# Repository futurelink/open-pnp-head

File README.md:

Versatile 4-nozzle PNP head controller
---

This controller was designed to be built into most of DIY pick-n-place machine heads.

### Features:
 - STM32F103C8T6 cheap MCU running on 72MHz
 - RS-485 control port
 - 4 rotary steppers running low-power STSPIN220 drivers
 - 2 up-down steppers running Pololu modules on your taste
 - 4 vacuum sensors to control part presence and place success
 - 4 isolated end-stop ports for home position identification
 - 4 isolated AO3400 MOSFET-driven ports to connect valves, solenoids etc.
 - head top light either WS2812 or LED-strip (5 or 12v)
 - Small size 80x65mm
 - No parts smaller than 0603 so can be hand-built.

### Board render:

### Disclaimer

This project is still in development, and it's not production ready.

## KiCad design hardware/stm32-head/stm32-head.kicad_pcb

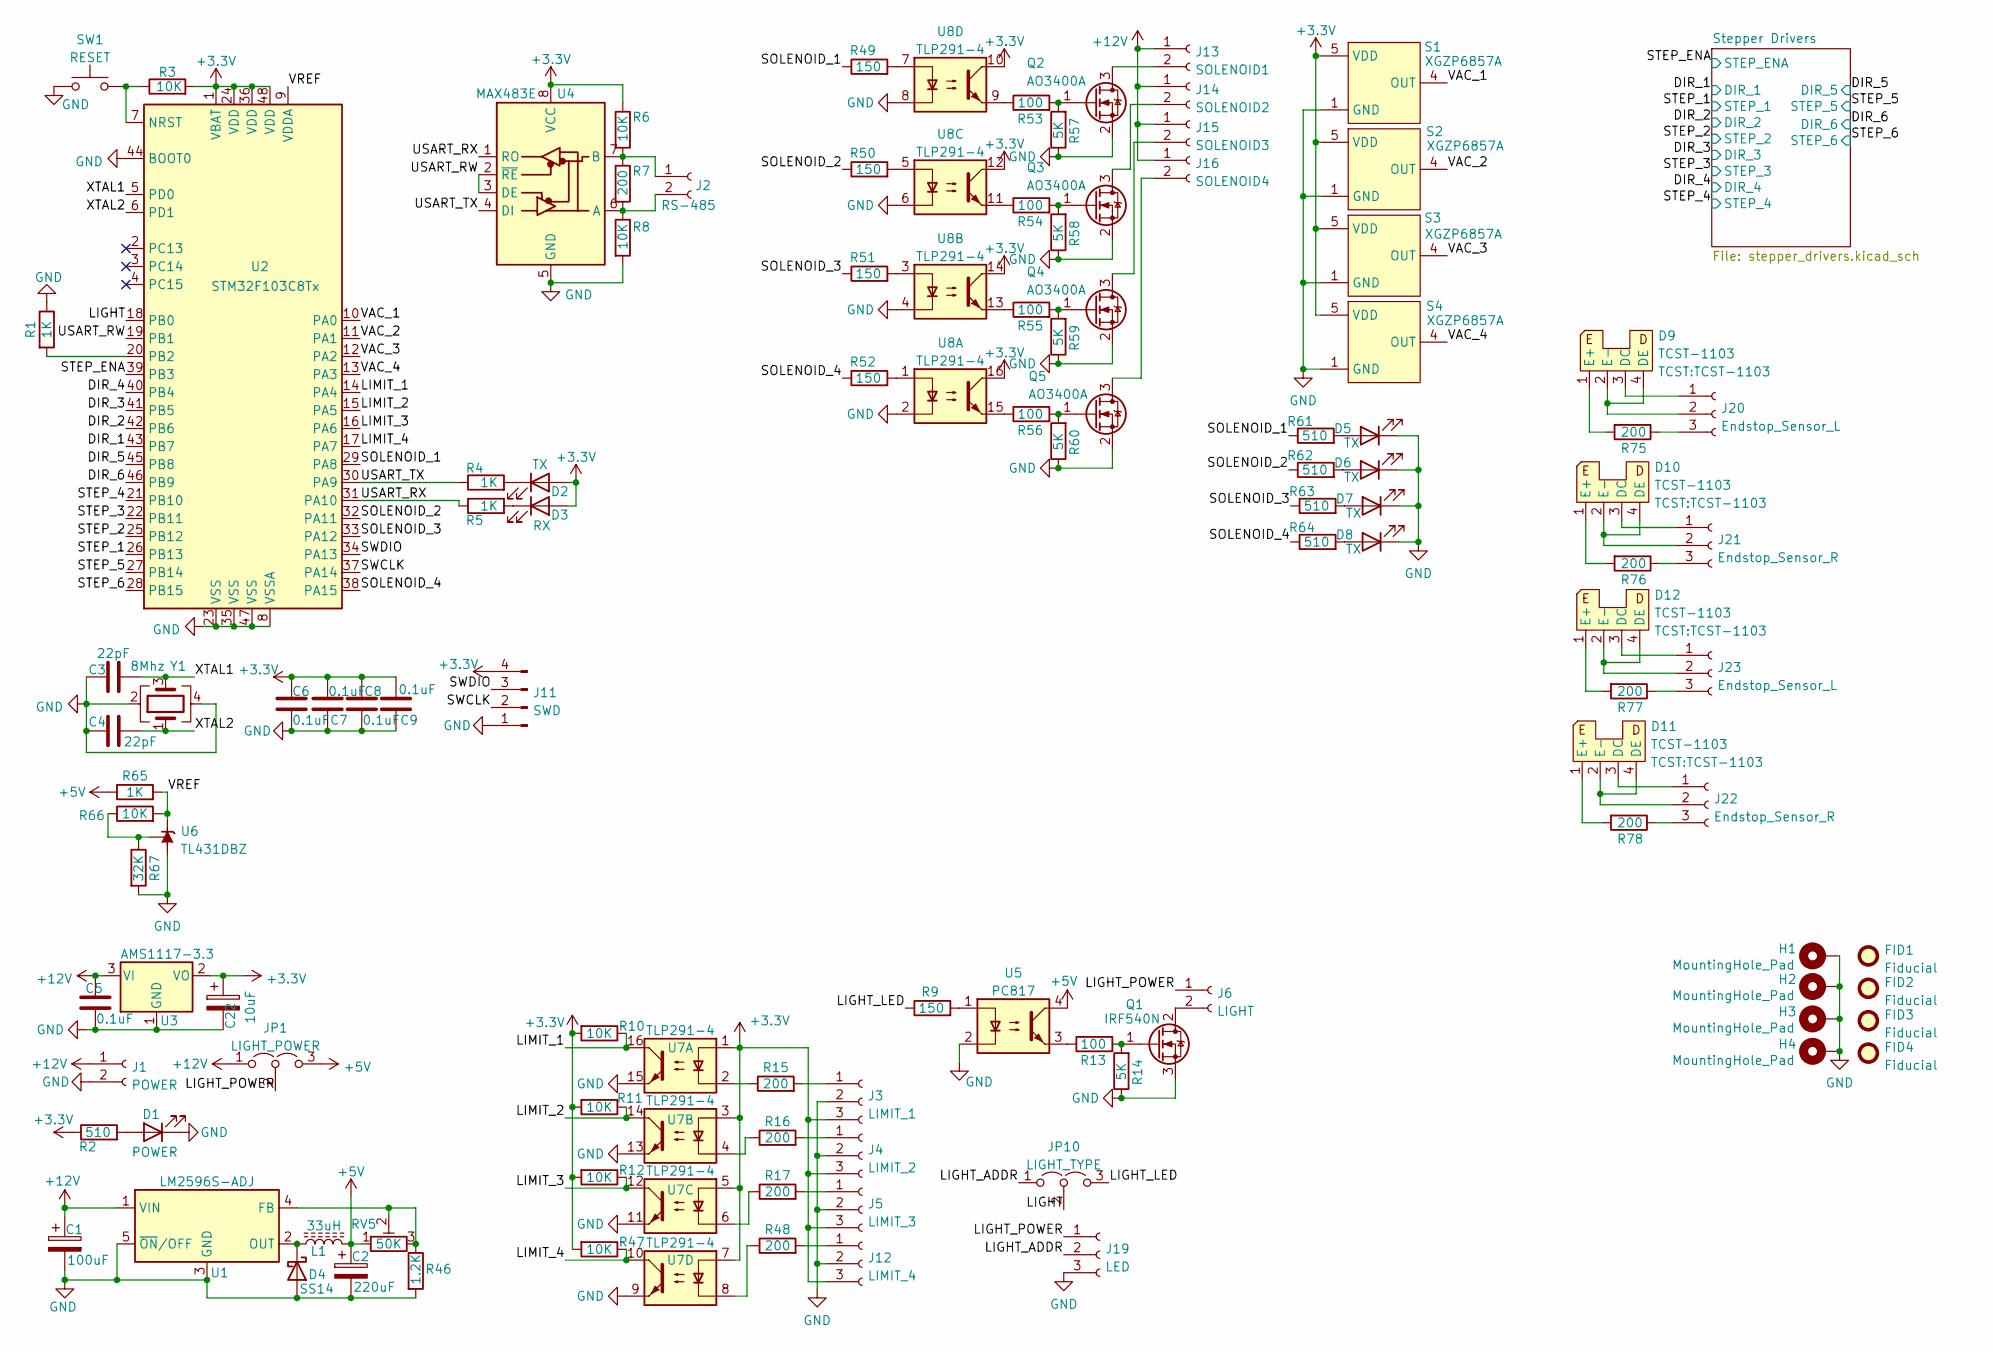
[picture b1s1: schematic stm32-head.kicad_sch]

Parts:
C1: 100uF; CP_Elec_6.3x5.9
C2: 220uF; CP_EIA-7343-31_Kemet-D
C3, C4: 22pF; C_0603_1608Metric
C5, C6, C7, C8, C9: 0.1uF; C_0603_1608Metric
C22: 10uF; CP_EIA-3216-12_Kemet-S
D1: POWER; LED_0603_1608Metric
D2, D5, D6, D7, D8: TX; LED_0603_1608Metric
D3: RX; LED_0603_1608Metric
D4: SS14; D_SMB
D9, D10, D11, D12: TCST-1103
FID1, FID2, FID3, FID4: Fiducial; Fiducial_0.5mm_Mask1mm
H1, H2, H3, H4: MountingHole_Pad; MountingHole_2.5mm_Pad_Via
J1: POWER; JST_XH_B2B-XH-A_1x02_P2.50mm_Vertical
J2: RS-485; JST_EH_B2B-EH-A_1x02_P2.50mm_Vertical
J3: LIMIT_1; JST_GH_BM03B-GHS-TBT_1x03-1MP_P1.25mm_Vertical
J4: LIMIT_2; JST_GH_BM03B-GHS-TBT_1x03-1MP_P1.25mm_Vertical
J5: LIMIT_3; JST_GH_BM03B-GHS-TBT_1x03-1MP_P1.25mm_Vertical
J6: LIGHT; JST_GH_BM02B-GHS-TBT_1x02-1MP_P1.25mm_Vertical
J11: SWD; JST_EH_B4B-EH-A_1x04_P2.50mm_Vertical
J12: LIMIT_4; JST_GH_BM03B-GHS-TBT_1x03-1MP_P1.25mm_Vertical
J13: SOLENOID1; JST_EH_B2B-EH-A_1x02_P2.50mm_Vertical
J14: SOLENOID2; JST_EH_B2B-EH-A_1x02_P2.50mm_Vertical
J15: SOLENOID3; JST_EH_B2B-EH-A_1x02_P2.50mm_Vertical
J16: SOLENOID4; JST_EH_B2B-EH-A_1x02_P2.50mm_Vertical
J19: LED; JST_EH_B3B-EH-A_1x03_P2.50mm_Vertical
J20, J23: Endstop_Sensor_L; JST_GH_SM03B-GHS-TB_1x03-1MP_P1.25mm_Horizontal
J21, J22: Endstop_Sensor_R; JST_GH_SM03B-GHS-TB_1x03-1MP_P1.25mm_Horizontal
JP1: LIGHT_POWER; PinHeader_1x03_P2.54mm_Vertical
JP10: LIGHT_TYPE; PinHeader_1x03_P2.54mm_Vertical
L1: 33uH; L_6.3x6.3_H3
Q1: IRF540N; TO-252-3_TabPin2
Q2, Q3, Q4, Q5: AO3400A; SOT-23
R1, R4, R5, R65: 1K; R_0603_1608Metric
R2, R61, R62, R63, R64: 510; R_0603_1608Metric
R3, R6, R8, R10, R11, R12, R47, R66: 10K; R_0603_1608Metric
R7, R15, R16, R17, R48, R75, R76, R77, R78: 200; R_0603_1608Metric
R9, R49, R50, R51, R52: 150; R_0603_1608Metric
R13, R53, R54, R55, R56: 100; R_0603_1608Metric
R14, R57, R58, R59, R60: 5K; R_0603_1608Metric
R46: 1.2K; R_0603_1608Metric
R67: 32K; R_0603_1608Metric
RV5: 50K; Potentiometer_Bourns_TC33X_Vertical
S1, S2, S3, S4: XGZP6857A; XGZP_Sensor_THT
SW1: RESET; SW_SPST_FSMSM
U1: LM2596S-ADJ; TO-263-5_TabPin3
U2: STM32F103C8Tx; LQFP-48_7x7mm_P0.5mm
U3: AMS1117-3.3; SOT-223-3_TabPin2
U4: MAX483E; SO-8_3.9x4.9mm_P1.27mm
U5: PC817; DIP-4_W7.62mm
U6: TL431DBZ; SOT-23
U7, U8: TLP291-4; SOIC-16_4.55x10.3mm_P1.27mm
Y1: 8Mhz; Crystal_SMD_3225-4Pin_3.2x2.5mm

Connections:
+3.3V: C6.2, C7.2, C8.2, C9.2, C22.1, D2.2 (A), D3.2 (A), J3.3, J4.3, J5.3, J11.4, J12.3, R2.1, R3.2, R6.1, R10.2, R11.2, R12.2, R47.2, S1.5 (VDD), S2.5 (VDD), S3.5 (VDD), S4.5 (VDD), U2.1 (VBAT), U2.24 (VDD), U2.36 (VDD), U2.48 (VDD), U3.2 (VO), U4.8 (VCC), U7.1, U7.3, U7.5, U7.7, U8.10, U8.12, U8.14, U8.16; also elsewhere on the board
+5V: C2.1, JP1.3 (B), L1.2, R65.1, RV5.1, U5.4; also elsewhere on the board
+12V: C1.1, C5.2, J1.1, J13.1, J14.1, J15.1, J16.1, JP1.1 (A), U1.1 (VIN), U3.3 (VI); also elsewhere on the board
/DIR_1: U2.43 (PB7); also elsewhere on the board
/DIR_2: U2.42 (PB6); also elsewhere on the board
/DIR_3: U2.41 (PB5); also elsewhere on the board
/DIR_4: U2.40 (PB4); also elsewhere on the board
/DIR_5: U2.45 (PB8); also elsewhere on the board
/DIR_6: U2.46 (PB9); also elsewhere on the board
/LIGHT: JP10.2 (C), U2.18 (PB0)
/LIGHT_ADDR: J19.2, JP10.1 (A)
/LIGHT_LED: JP10.3 (B), R9.1
/LIGHT_POWER: J6.1, J19.1, JP1.2 (C)
/LIMIT_1: R10.1, U2.14 (PA4), U7.16
/LIMIT_2: R11.1, U2.15 (PA5), U7.14
/LIMIT_3: R12.1, U2.16 (PA6), U7.12
/LIMIT_4: R47.1, U2.17 (PA7), U7.10
/SOLENOID_1: R49.1, R61.1, U2.29 (PA8)
/SOLENOID_2: R50.1, R62.1, U2.32 (PA11)
/SOLENOID_3: R51.1, R63.1, U2.33 (PA12)
/SOLENOID_4: R52.1, R64.1, U2.38 (PA15)
/STEP_1: U2.26 (PB13); also elsewhere on the board
/STEP_2: U2.25 (PB12); also elsewhere on the board
/STEP_3: U2.22 (PB11); also elsewhere on the board
/STEP_4: U2.21 (PB10); also elsewhere on the board
/STEP_5: U2.27 (PB14); also elsewhere on the board
/STEP_6: U2.28 (PB15); also elsewhere on the board
/STEP_ENA: U2.39 (PB3); also elsewhere on the board
/SWCLK: J11.2, U2.37 (PA14)
/SWDIO: J11.3, U2.34 (PA13)
/USART_RW: U2.19 (PB1), U4.2 (~RE), U4.3 (DE)
/USART_RX: R5.1, U2.31 (PA10), U4.1 (RO)
/USART_TX: R4.1, U2.30 (PA9), U4.4 (DI)
/VAC_1: S1.4 (OUT), U2.10 (PA0)
/VAC_2: S2.4 (OUT), U2.11 (PA1)
/VAC_3: S3.4 (OUT), U2.12 (PA2)
/VAC_4: S4.4 (OUT), U2.13 (PA3)
/VREF: R65.2, R66.2, U2.9 (VDDA), U6.1 (K)
/XTAL1: C3.2, U2.5 (PD0), Y1.3
/XTAL2: C4.2, U2.6 (PD1), Y1.1
GND: C1.2, C2.2, C3.1, C4.1, C5.1, C6.1, C7.1, C8.1, C9.1, C22.2, D1.1 (K), D4.2 (A), D5.1 (K), D6.1 (K), D7.1 (K), D8.1 (K), H1.1, H2.1, H3.1, H4.1, J1.2, J3.2, J4.2, J5.2, J11.1, J12.2, J19.3, Q1.3 (S), Q2.2 (S), Q3.2 (S), Q4.2 (S), Q5.2 (S), R1.1, R8.2, R14.1, R46.2, R57.1, R58.1, R59.1, R60.1, R67.2, S1.1 (GND), S2.1 (GND), S3.1 (GND), S4.1 (GND), SW1.1, U1.3 (GND), U1.5 (~ON/OFF), U2.8 (VSSA), U2.23 (VSS), U2.35 (VSS), U2.44 (BOOT0), U2.47 (VSS), U3.1 (GND), U4.5 (GND), U5.2, U6.3 (A), U7.9, U7.11, U7.13, U7.15, U8.2, U8.4, U8.6, U8.8, Y1.2, Y1.4; also elsewhere on the board
unnamed: D1.2 (A), R2.2
unnamed: D2.1 (K), R4.2
unnamed: D3.1 (K), R5.2
unnamed: D4.1 (K), L1.1, U1.2 (OUT)
unnamed: D5.2 (A), R61.2
unnamed: D6.2 (A), R62.2
unnamed: D7.2 (A), R63.2
unnamed: D8.2 (A), R64.2
unnamed: D9.1 (E+), R75.2
unnamed: D9.2 (E-), D9.4 (DE), J20.2
unnamed: D9.3 (DC), J20.1
unnamed: D10.1 (E+), R76.2
unnamed: D10.2 (E-), D10.4 (DE), J21.2
unnamed: D10.3 (DC), J21.1
unnamed: D11.1 (E+), R78.2
unnamed: D11.2 (E-), D11.4 (DE), J22.2
unnamed: D11.3 (DC), J22.1
unnamed: D12.1 (E+), R77.2
unnamed: D12.2 (E-), D12.4 (DE), J23.2
unnamed: D12.3 (DC), J23.1
unnamed: J2.1, R6.2, R7.1, U4.7 (B)
unnamed: J2.2, R7.2, R8.1, U4.6 (A)
unnamed: J3.1, R15.2
unnamed: J4.1, R16.2
unnamed: J5.1, R17.2
unnamed: J6.2, Q1.2 (D)
unnamed: J12.1, R48.2
unnamed: J13.2, Q2.3 (D)
unnamed: J14.2, Q3.3 (D)
unnamed: J15.2, Q4.3 (D)
unnamed: J16.2, Q5.3 (D)
unnamed: J20.3, R75.1
unnamed: J21.3, R76.1
unnamed: J22.3, R78.1
unnamed: J23.3, R77.1
unnamed: Q1.1 (G), R13.2, R14.2
unnamed: Q2.1 (G), R53.2, R57.2
unnamed: Q3.1 (G), R54.2, R58.2
unnamed: Q4.1 (G), R55.2, R59.2
unnamed: Q5.1 (G), R56.2, R60.2
unnamed: R1.2, U2.20 (PB2)
unnamed: R3.1, SW1.2, U2.7 (NRST)
unnamed: R9.2, U5.1
unnamed: R13.1, U5.3
unnamed: R15.1, U7.2
unnamed: R16.1, U7.4
unnamed: R17.1, U7.6
unnamed: R46.1, RV5.2, RV5.3, U1.4 (FB)
unnamed: R48.1, U7.8
unnamed: R49.2, U8.7
unnamed: R50.2, U8.5
unnamed: R51.2, U8.3
unnamed: R52.2, U8.1
unnamed: R53.1, U8.9
unnamed: R54.1, U8.11
unnamed: R55.1, U8.13
unnamed: R56.1, U8.15
unnamed: R66.1, R67.1, U6.2 (REF)

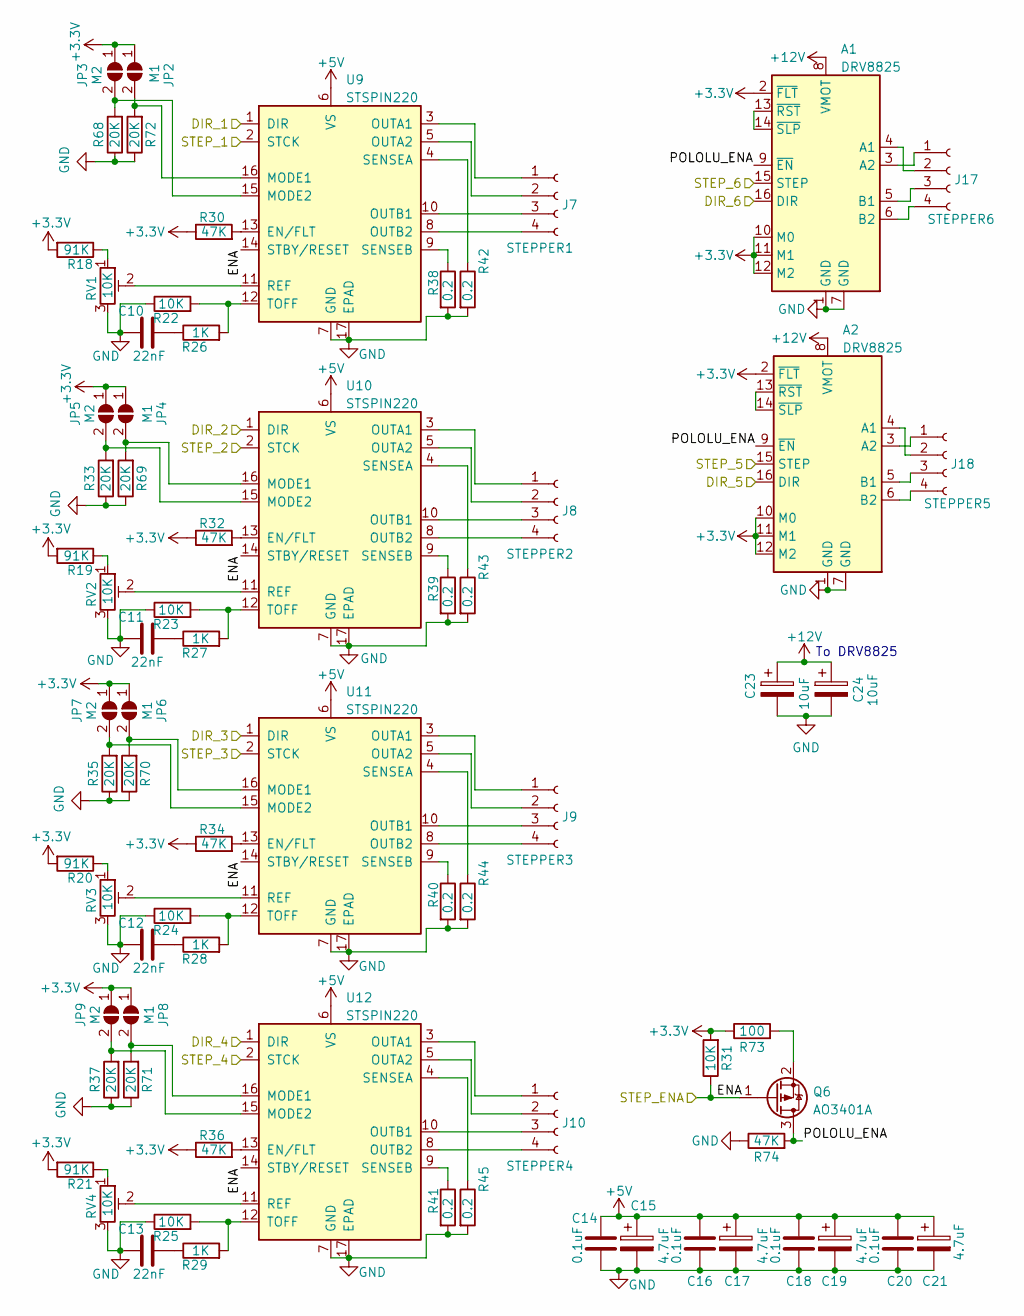
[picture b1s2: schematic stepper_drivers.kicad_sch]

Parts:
A1, A2: DRV8825; Pololu_Breakout-16_15.2x20.3mm
C10, C11, C12, C13: 22nF; C_0603_1608Metric
C14, C16, C18, C20: 0.1uF; C_0603_1608Metric
C15, C17, C19, C21: 4.7uF; CP_EIA-3216-10_Kemet-I
C23, C24: 10uF; CP_Elec_6.3x5.9
J7: STEPPER1; JST_GH_SM04B-GHS-TB_1x04-1MP_P1.25mm_Horizontal
J8: STEPPER2; JST_GH_SM04B-GHS-TB_1x04-1MP_P1.25mm_Horizontal
J9: STEPPER3; JST_GH_SM04B-GHS-TB_1x04-1MP_P1.25mm_Horizontal
J10: STEPPER4; JST_GH_SM04B-GHS-TB_1x04-1MP_P1.25mm_Horizontal
J17: STEPPER6; JST_GH_SM04B-GHS-TB_1x04-1MP_P1.25mm_Horizontal
J18: STEPPER5; JST_GH_SM04B-GHS-TB_1x04-1MP_P1.25mm_Horizontal
JP2, JP4, JP6, JP8: M1; SolderJumper-2_P1.3mm_Open_RoundedPad1.0x1.5mm
JP3, JP5, JP7, JP9: M2; SolderJumper-2_P1.3mm_Open_RoundedPad1.0x1.5mm
Q6: AO3401A; SOT-23
R18, R19, R20, R21: 91K; R_0603_1608Metric
R22, R23, R24, R25, R31: 10K; R_0603_1608Metric
R26, R27, R28, R29: 1K; R_0603_1608Metric
R30, R32, R34, R36, R74: 47K; R_0603_1608Metric
R33, R35, R37, R68, R69, R70, R71, R72: 20K; R_0603_1608Metric
R38, R39, R40, R41, R42, R43, R44, R45: 0.2; R_1206_3216Metric
R73: 100; R_0603_1608Metric
RV1, RV2, RV3, RV4: 10K; Potentiometer_Bourns_TC33X_Vertical
U9, U10, U11, U12: STSPIN220; VQFN-16-1EP_3x3mm_P0.5mm_EP1.8x1.8mm

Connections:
+3.3V: A1.2 (~FLT), A1.10 (M0), A1.11 (M1), A1.12 (M2), A2.2 (~FLT), A2.10 (M0), A2.11 (M1), A2.12 (M2), JP2.1 (A), JP3.1 (A), JP4.1 (A), JP5.1 (A), JP6.1 (A), JP7.1 (A), JP8.1 (A), JP9.1 (A), R18.2, R19.2, R20.2, R21.2, R30.1, R31.2, R32.1, R34.1, R36.1, R73.1; also elsewhere on the board
+5V: C14.1, C15.1, C16.1, C17.1, C18.1, C19.1, C20.1, C21.1, U9.6 (VS), U10.6 (VS), U11.6 (VS), U12.6 (VS); also elsewhere on the board
+12V: A1.8 (VMOT), A2.8 (VMOT), C23.1, C24.1; also elsewhere on the board
/DIR_1: U9.1 (DIR); also elsewhere on the board
/DIR_2: U10.1 (DIR); also elsewhere on the board
/DIR_3: U11.1 (DIR); also elsewhere on the board
/DIR_4: U12.1 (DIR); also elsewhere on the board
/DIR_5: A2.16 (DIR); also elsewhere on the board
/DIR_6: A1.16 (DIR); also elsewhere on the board
/STEP_1: U9.2 (STCK); also elsewhere on the board
/STEP_2: U10.2 (STCK); also elsewhere on the board
/STEP_3: U11.2 (STCK); also elsewhere on the board
/STEP_4: U12.2 (STCK); also elsewhere on the board
/STEP_5: A2.15 (STEP); also elsewhere on the board
/STEP_6: A1.15 (STEP); also elsewhere on the board
/STEP_ENA: Q6.1 (G), R31.1, U9.14 (STBY/RESET), U10.14 (STBY/RESET), U11.14 (STBY/RESET), U12.14 (STBY/RESET); also elsewhere on the board
/Stepper Drivers/POLOLU_ENA: A1.9 (~EN), A2.9 (~EN), Q6.3 (D), R74.2
GND: A1.1 (GND), A1.7 (GND), A2.1 (GND), A2.7 (GND), C10.1, C11.1, C12.1, C13.1, C14.2, C15.2, C16.2, C17.2, C18.2, C19.2, C20.2, C21.2, C23.2, C24.2, R22.1, R23.1, R24.1, R25.1, R33.1, R35.1, R37.1, R38.2, R39.2, R40.2, R41.2, R42.2, R43.2, R44.2, R45.2, R68.1, R69.1, R70.1, R71.1, R72.1, R74.1, RV1.3, RV2.3, RV3.3, RV4.3, U9.7 (GND), U9.17 (EPAD), U10.7 (GND), U10.17 (EPAD), U11.7 (GND), U11.17 (EPAD), U12.7 (GND), U12.17 (EPAD); also elsewhere on the board
unnamed: A1.3 (A2), J17.1
unnamed: A1.4 (A1), J17.2
unnamed: A1.5 (B1), J17.3
unnamed: A1.6 (B2), J17.4
unnamed: A1.13 (~RST), A1.14 (~SLP)
unnamed: A2.3 (A2), J18.1
unnamed: A2.4 (A1), J18.2
unnamed: A2.5 (B1), J18.3
unnamed: A2.6 (B2), J18.4
unnamed: A2.13 (~RST), A2.14 (~SLP)
unnamed: C10.2, R26.1
unnamed: C11.2, R27.1
unnamed: C12.2, R28.1
unnamed: C13.2, R29.1
unnamed: J7.1, U9.3 (OUTA1)
unnamed: J7.2, U9.5 (OUTA2)
unnamed: J7.3, U9.10 (OUTB1)
unnamed: J7.4, U9.8 (OUTB2)
unnamed: J8.1, U10.3 (OUTA1)
unnamed: J8.2, U10.5 (OUTA2)
unnamed: J8.3, U10.10 (OUTB1)
unnamed: J8.4, U10.8 (OUTB2)
unnamed: J9.1, U11.3 (OUTA1)
unnamed: J9.2, U11.5 (OUTA2)
unnamed: J9.3, U11.10 (OUTB1)
unnamed: J9.4, U11.8 (OUTB2)
unnamed: J10.1, U12.3 (OUTA1)
unnamed: J10.2, U12.5 (OUTA2)
unnamed: J10.3, U12.10 (OUTB1)
unnamed: J10.4, U12.8 (OUTB2)
unnamed: JP2.2 (B), R72.2, U9.16 (MODE1)
unnamed: JP3.2 (B), R68.2, U9.15 (MODE2)
unnamed: JP4.2 (B), R69.2, U10.16 (MODE1)
unnamed: JP5.2 (B), R33.2, U10.15 (MODE2)
unnamed: JP6.2 (B), R70.2, U11.16 (MODE1)
unnamed: JP7.2 (B), R35.2, U11.15 (MODE2)
unnamed: JP8.2 (B), R71.2, U12.16 (MODE1)
unnamed: JP9.2 (B), R37.2, U12.15 (MODE2)
unnamed: Q6.2 (S), R73.2
unnamed: R18.1, RV1.1
unnamed: R19.1, RV2.1
unnamed: R20.1, RV3.1
unnamed: R21.1, RV4.1
unnamed: R22.2, R26.2, U9.12 (TOFF)
unnamed: R23.2, R27.2, U10.12 (TOFF)
unnamed: R24.2, R28.2, U11.12 (TOFF)
unnamed: R25.2, R29.2, U12.12 (TOFF)
unnamed: R30.2, U9.13 (EN/FLT)
unnamed: R32.2, U10.13 (EN/FLT)
unnamed: R34.2, U11.13 (EN/FLT)
unnamed: R36.2, U12.13 (EN/FLT)
unnamed: R38.1, U9.9 (SENSEB)
unnamed: R39.1, U10.9 (SENSEB)
unnamed: R40.1, U11.9 (SENSEB)
unnamed: R41.1, U12.9 (SENSEB)
unnamed: R42.1, U9.4 (SENSEA)
unnamed: R43.1, U10.4 (SENSEA)
unnamed: R44.1, U11.4 (SENSEA)
unnamed: R45.1, U12.4 (SENSEA)
unnamed: RV1.2, U9.11 (REF)
unnamed: RV2.2, U10.11 (REF)
unnamed: RV3.2, U11.11 (REF)
unnamed: RV4.2, U12.11 (REF)

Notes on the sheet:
To DRV8825

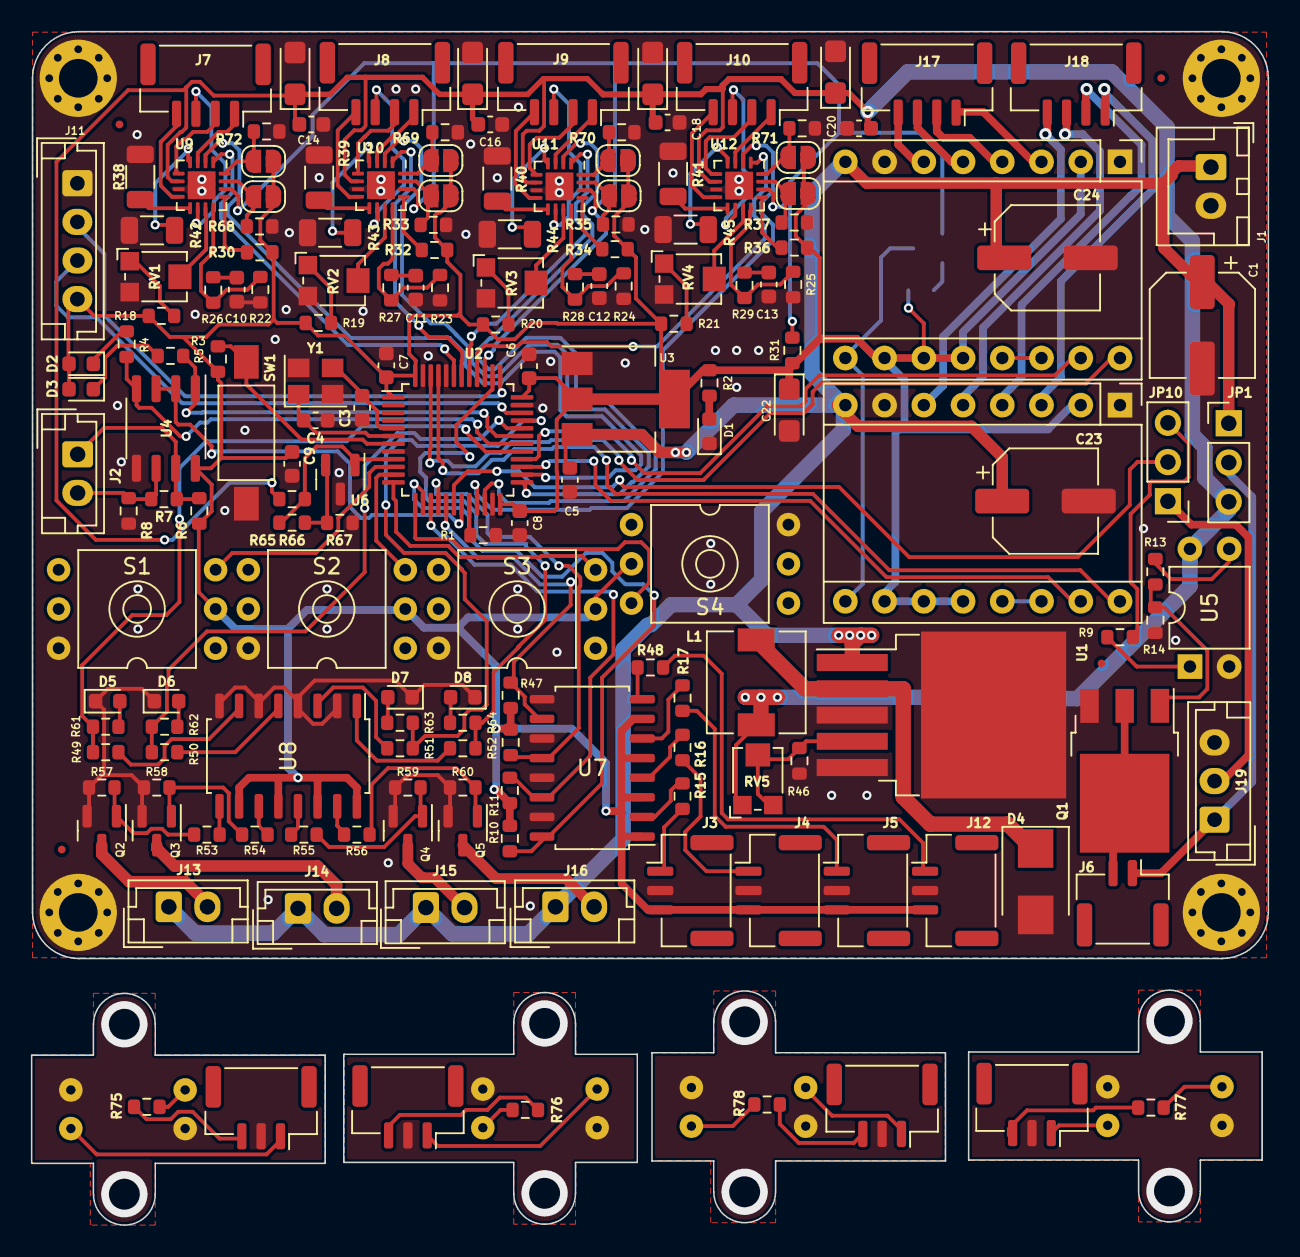
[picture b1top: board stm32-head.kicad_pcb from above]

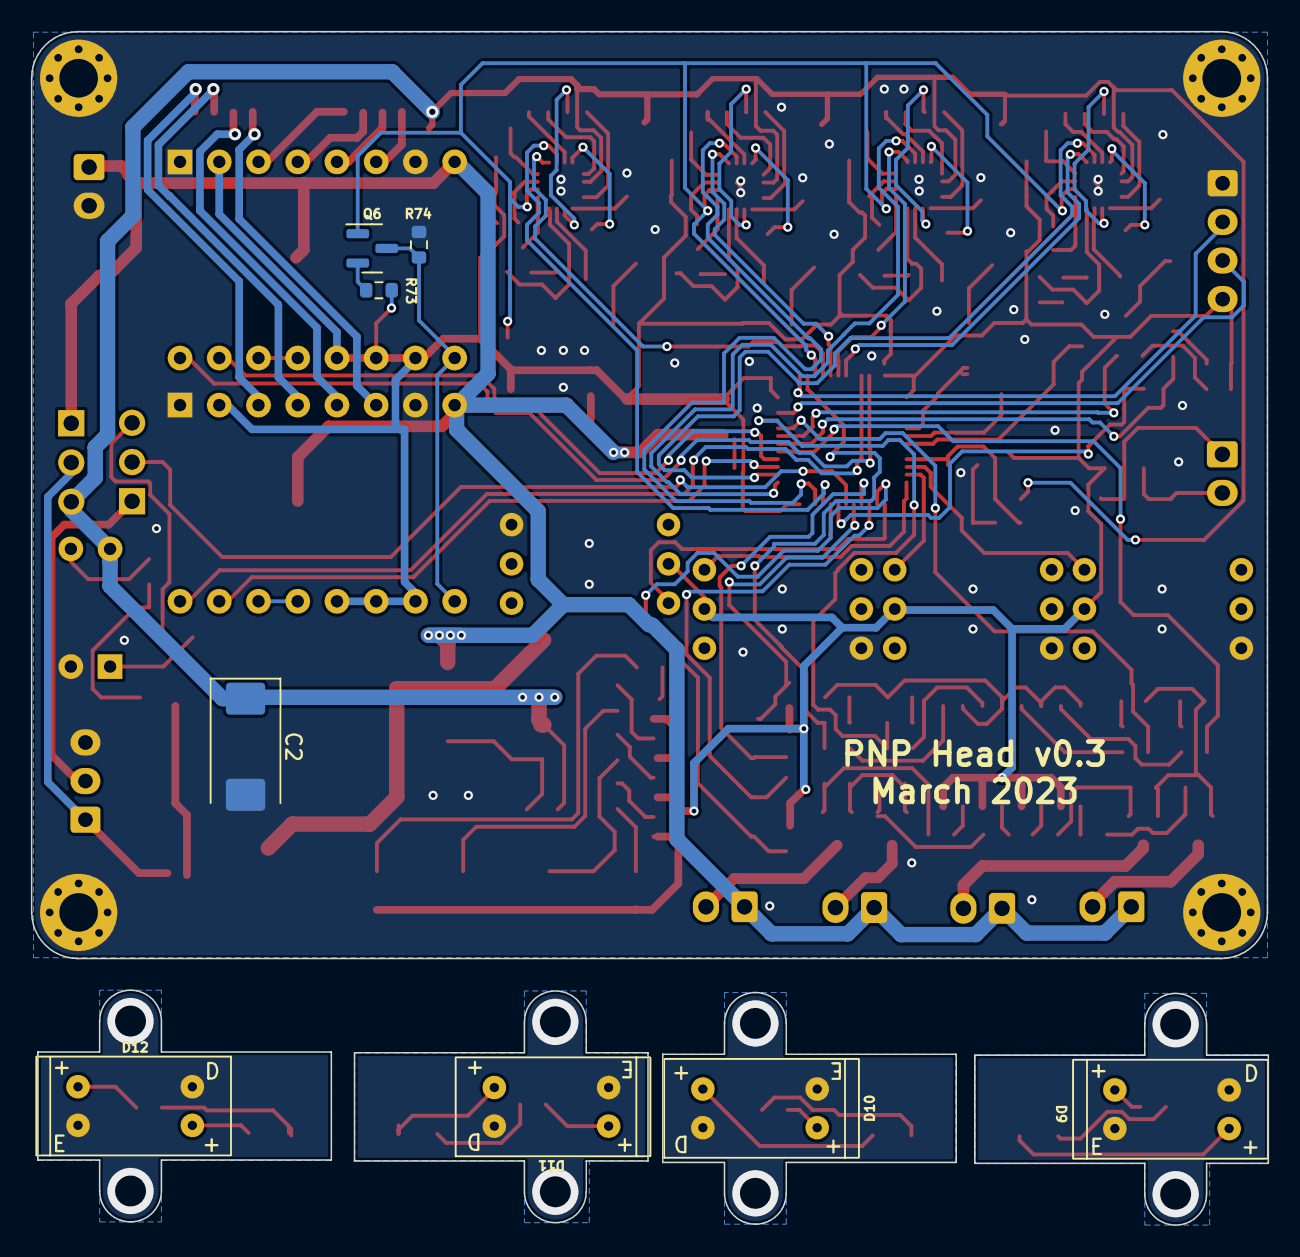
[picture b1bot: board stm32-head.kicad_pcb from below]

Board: 2 copper layers, 80.1 x 77.3 mm, 187 parts (8 on the bottom side), 163 nets.

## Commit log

2023-03-04 Board fixes
2023-03-05 HW fixes
2023-03-07 Some work on firmware
2023-03-08 Address LED light support.
2023-03-11 Some tweaks
2023-03-11 Disable steppers on movement end when in zero position.
2023-03-30 readme
2023-04-02 PCB v0.3 went to production
2023-04-10 - RS-485 timing fix - vacuum sensor read command
2023-04-25 modbus support development
